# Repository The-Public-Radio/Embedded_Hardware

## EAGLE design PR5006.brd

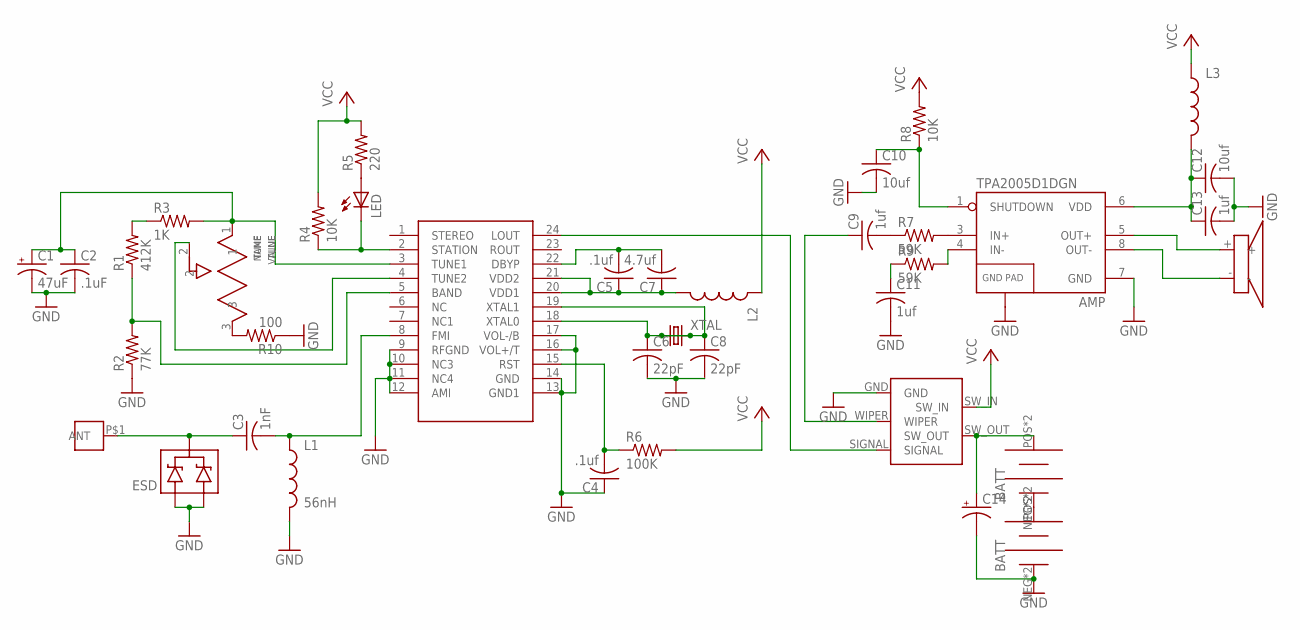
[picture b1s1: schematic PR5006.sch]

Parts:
AMP: TPA2005D1DGN; POWER-SOP8
C1: 47uF; E2-5
C2: .1uF; C0603
C3: 1nF; C0603
C4, C5: .1uf; C0603
C6, C8: 22pF; C0603
C7: 4.7uf; C0603
C9, C11, C13: 1uf; C0603
C10, C12: 10uf; C0603
C14: CPOL-USE2.5-5; E2,5-5
ESD: MMBZ27VCLT1; SOT23-3
L1: 56nH; 0603
L2, L3: INDUCTOR0603; 0603
LED: LEDCHIP-LED0603; CHIP-LED0603
R1: 412K; R0603
R2: 77K; R0603
R3: 1K; R0603
R4, R8: 10K; R0603
R5: 220; R0603
R6: 100K; R0603
R7, R9: 59K; R0603
R10: 100; R0603
SI4831: SI4831-SSOP-24
TUNE: TUNE; 64XR_BOURNS_TRIMPOT
U$1, U$2: BK-92_MPD_AA_BATT_CLIP
U$3: CE32A_DAYTON_SPKR
U$4: M3_SCREW_POST
U$5: P170_BOURNS_POT_SW
XTAL: CRYSTAL32-SMD; CRYSTAL-32KHZ-SMD

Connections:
GND: AMP.7 (GND), AMP.9 (GND), C1.-, C2.2, C4.1, C6.2, C8.2, C10.2, C11.2, C12.2, C13.2, C14.-, ESD.1 (A1), ESD.2 (A2), L1.2, R2.1, R10.1, SI4831.9 (RFGND), SI4831.10 (NC3), SI4831.11 (NC4), SI4831.12 (AMI), SI4831.13 (GND1), SI4831.14 (GND), SI4831.16 (VOL+/T), SI4831.17 (VOL-/B), U$2.NEG, U$2.NEG@2 (NEG), U$5.GND
unnamed: AMP.3 (IN+), R7.2
unnamed: AMP.4 (IN-), R9.2
unnamed: C11.1, R9.1
unnamed: C9.2, R7.1
unnamed: SI4831.24 (LOUT), U$5.SIGNAL
unnamed: C5.2, C7.2, SI4831.22 (DBYP)
unnamed: C8.1, SI4831.19 (XTAL1), XTAL.X1 (1)
unnamed: C4.2, R6.1, SI4831.15 (RST)
unnamed: LED.C, R4.1, SI4831.2 (STATION)
unnamed: C6.1, SI4831.18 (XTAL0), XTAL.X2 (2)
unnamed: LED.A, R5.1
unnamed: SI4831.4 (TUNE2), TUNE.2
unnamed: R1.1, R2.2, SI4831.5 (BAND)
unnamed: U$1.NEG, U$1.NEG@2 (NEG), U$2.POS, U$2.POS@2 (POS)
unnamed: C3.2, L1.1, SI4831.8 (FMI)
unnamed: C5.1, C7.1, L2.2, SI4831.20 (VDD1), SI4831.21 (VDD2)
unnamed: AMP.6 (VDD), C12.1, C13.1, L3.2
unnamed: AMP.1 (SHUTDOWN), C10.1, R8.1
unnamed 19: C3.1, ESD.3 (C), U$4.P$1; also elsewhere on the board
unnamed: R1.2, R3.1
unnamed: C1.+, C2.1, R3.2, SI4831.3 (TUNE1), TUNE.1
unnamed: AMP.5 (OUT+), U$3.+
unnamed: AMP.8 (OUT-), U$3.-
unnamed: C9.1, U$5.WIPER
unnamed: R10.2, TUNE.3
unnamed: C14.+, U$1.POS, U$1.POS@2 (POS), U$5.SW_OUT
VCC: L2.1, L3.1, R4.2, R5.2, R6.2, R8.2, U$5.SW_IN

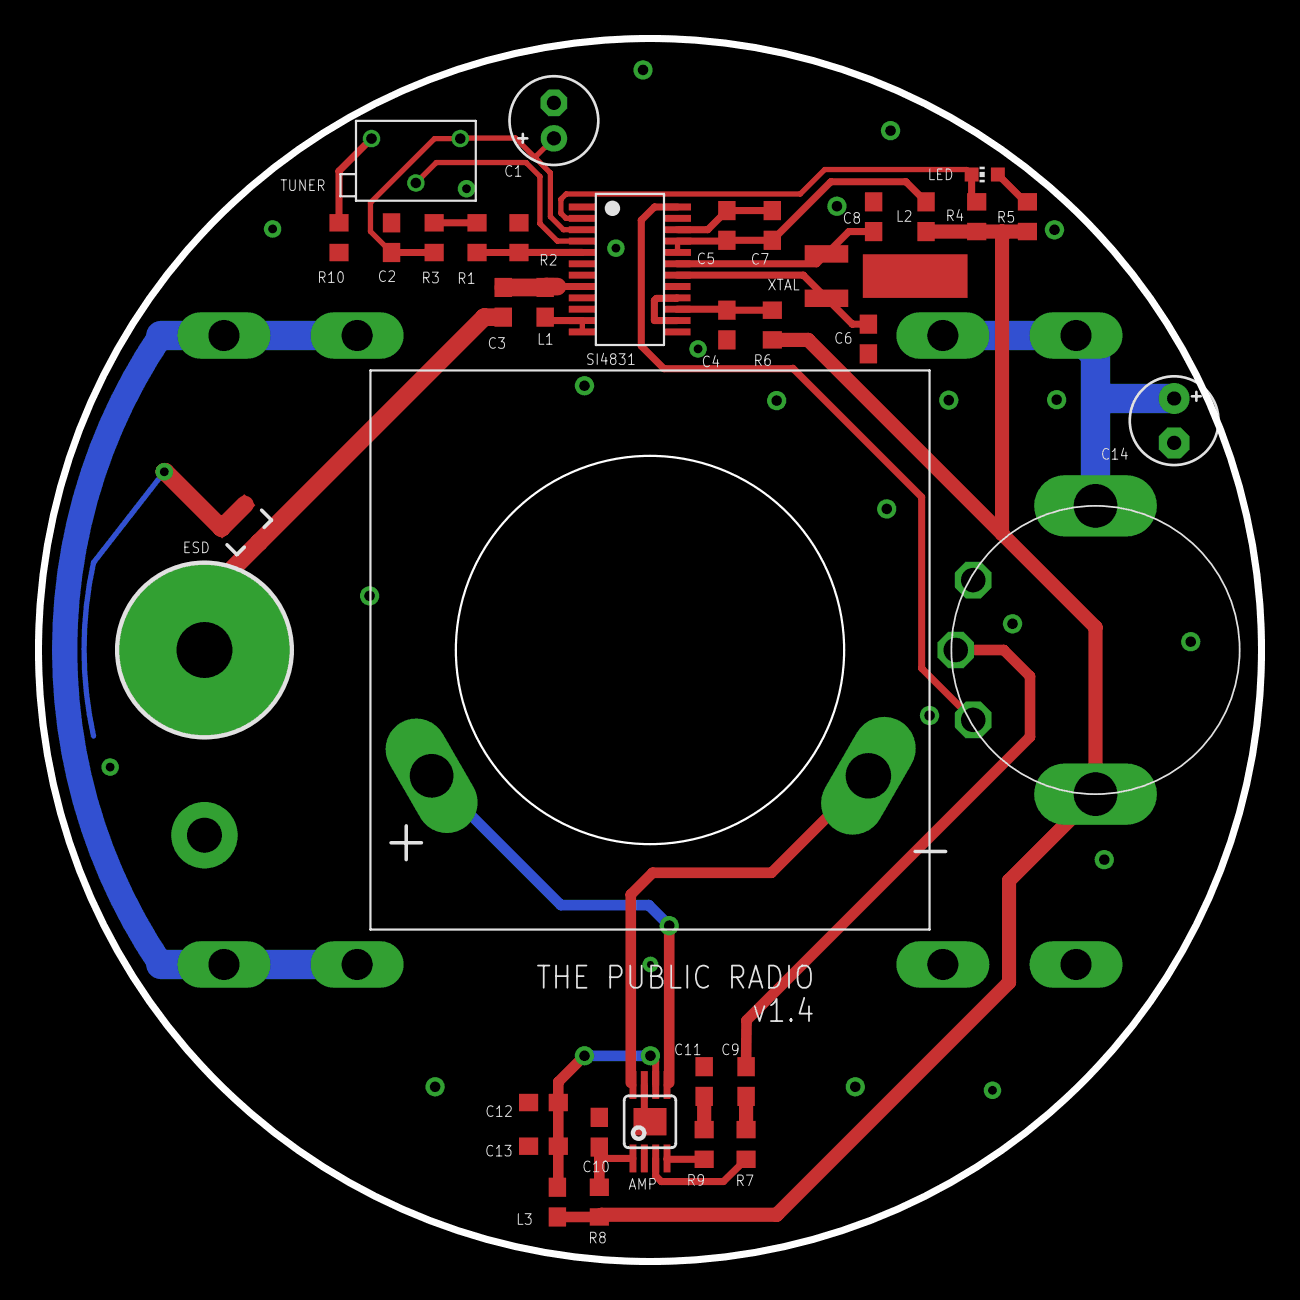
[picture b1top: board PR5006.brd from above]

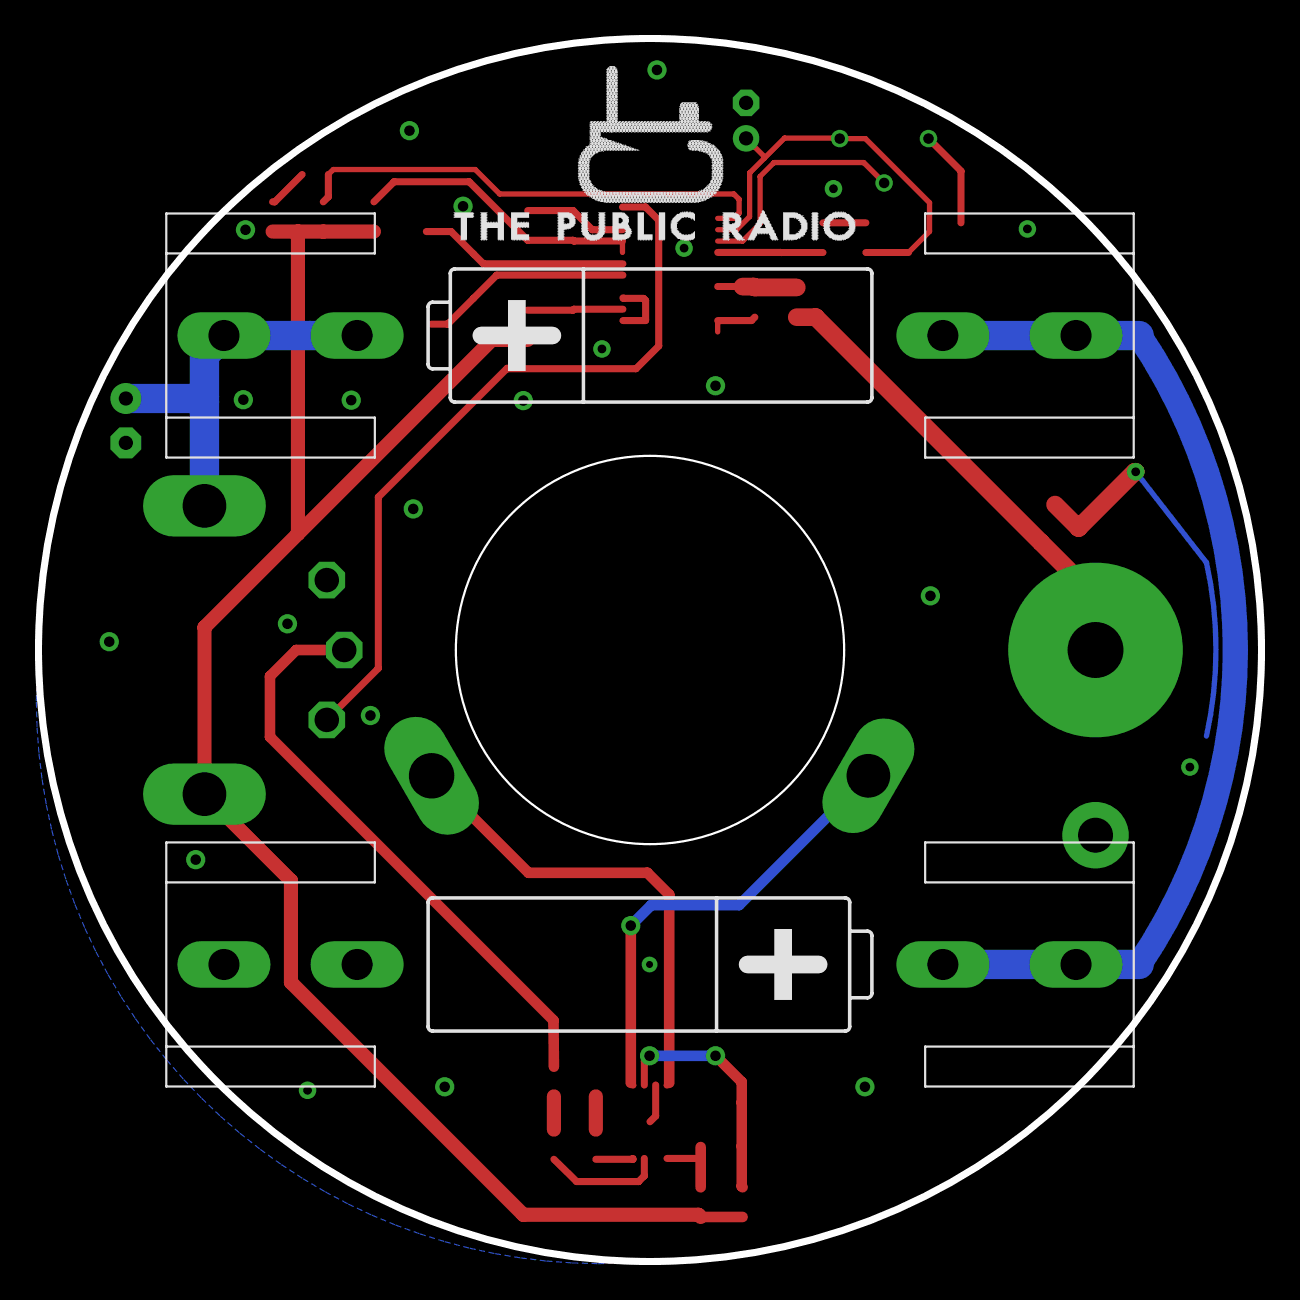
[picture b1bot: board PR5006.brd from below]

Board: 2 copper layers, 70.0 x 70.0 mm, 38 parts (2 on the bottom side), 28 nets.

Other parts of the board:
ANT: M3_SCREW_POST

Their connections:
unnamed 19: ANT.P$1; also elsewhere on the board

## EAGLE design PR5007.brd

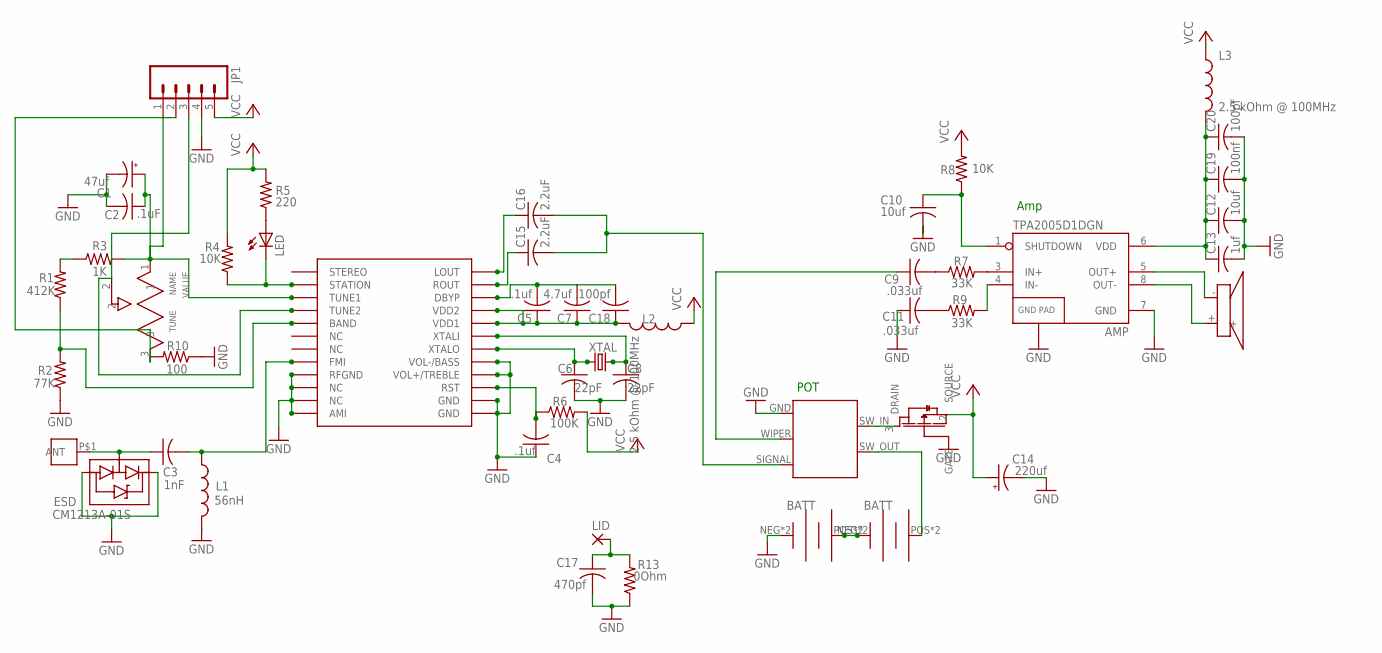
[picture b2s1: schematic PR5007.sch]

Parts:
AMP: TPA2005D1DGN; POWER-SOP8
ANT: M3_SCREW_POST
C1: 47uf; E2-5
C2: .1uF; C0603
C3: 1nF; C0603
C4, C5: .1uf; C0603
C6, C8: 22pF; C0603
C7: 4.7uf; C0603
C9, C11: .033uf; C0603
C10, C12: 10uf; C0603
C13: 1uf; C0603
C14: 220uf; E2-5
C15, C16: 2.2uF; C0603
C17: 470pf; C0805
C18, C20: 100pf; C0603
C19: 100nf; C0603
ESD: CM1213A-01S; SOT23-3
FET: SI2333DDS
JP1: M05LOCK; 1X05_LOCK
L1: 56nH; 0603
L2, L3: 2.5 kOhm @ 100MHz; 0603
LED: LEDCHIPLED_0805; CHIPLED_0805
LID: 2,54/1,0
R1: 412K; R0603
R2: 77K; R0603
R3: 1K; R0603
R4, R8: 10K; R0603
R5: 220; R0603
R6: 100K; R0603
R7, R9: 33K; R0603
R10: 100; R0603
R13: 0Ohm; R0603
TUNE: TUNE; 64XR_BOURNS_TRIMPOT
U$1, U$2: BK-92_MPD_AA_BATT_CLIP
U$3: CE32A_DAYTON_SPKR
U$4: SI4831_FM_IC
U$5: RV170SF_TAIWANA_POT_SW
XTAL: CRYSTAL32-SMD; CRYSTAL-32KHZ-SMD

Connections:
GND: AMP.7 (GND), AMP.9 (GND), C1.-, C2.2, C4.1, C6.2, C8.2, C10.2, C11.1, C12.2, C13.2, C14.-, C17.2, C19.2, C20.2, ESD.2 (VP), ESD.3 (VN), FET.1 (GATE), JP1.4, L1.2, R2.1, R10.1, R13.1, U$2.NEG, U$2.NEG@2 (NEG), U$4.AMI, U$4.GND, U$4.GND@2 (GND), U$4.NC@3 (NC), U$4.NC@4 (NC), U$4.RFGND, U$4.VOL+/TREBLE, U$4.VOL-/BASS, U$5.GND
unnamed: AMP.3 (IN+), R7.2
unnamed: AMP.4 (IN-), R9.2
unnamed: C11.2, R9.1
unnamed: C9.2, R7.1
unnamed: C15.2, C16.2, U$5.SIGNAL
unnamed: C5.2, C7.2, C18.2, U$4.DBYP
unnamed: C8.1, U$4.XTALI, XTAL.X1 (1)
unnamed: C4.2, R6.1, U$4.RST
unnamed: LED.C, R4.1, U$4.STATION
unnamed: C6.1, U$4.XTALO, XTAL.X2 (2)
unnamed: LED.A, R5.1
unnamed: JP1.3, TUNE.2, U$4.TUNE2
unnamed: R1.1, R2.2, U$4.BAND
unnamed: U$1.NEG, U$1.NEG@2 (NEG), U$2.POS, U$2.POS@2 (POS)
unnamed: C3.2, L1.1, U$4.FMI
unnamed: C5.1, C7.1, C18.1, L2.2, U$4.VDD1, U$4.VDD2
unnamed: AMP.6 (VDD), C12.1, C13.1, C19.1, C20.1, L3.2
unnamed: AMP.1 (SHUTDOWN), C10.1, R8.1
unnamed: ANT.P$1, C3.1, ESD.1 (CH)
unnamed: R1.2, R3.1
unnamed: U$1.POS, U$1.POS@2 (POS), U$5.SW_OUT
unnamed: C1.+, C2.1, JP1.1, R3.2, TUNE.1, U$4.TUNE1
unnamed: AMP.5 (OUT+), U$3.-
unnamed: AMP.8 (OUT-), U$3.+
unnamed: C9.1, U$5.WIPER
unnamed: JP1.2, R10.2, TUNE.3
unnamed: FET.3 (DRAIN), U$5.SW_IN
unnamed: C15.1, U$4.ROUT
unnamed: C16.1, U$4.LOUT
unnamed: C17.1, LID.1, R13.2
VCC: C14.+, FET.2 (SOURCE), JP1.5, L2.1, L3.1, R4.2, R5.2, R6.2, R8.2

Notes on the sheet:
Amp
POT

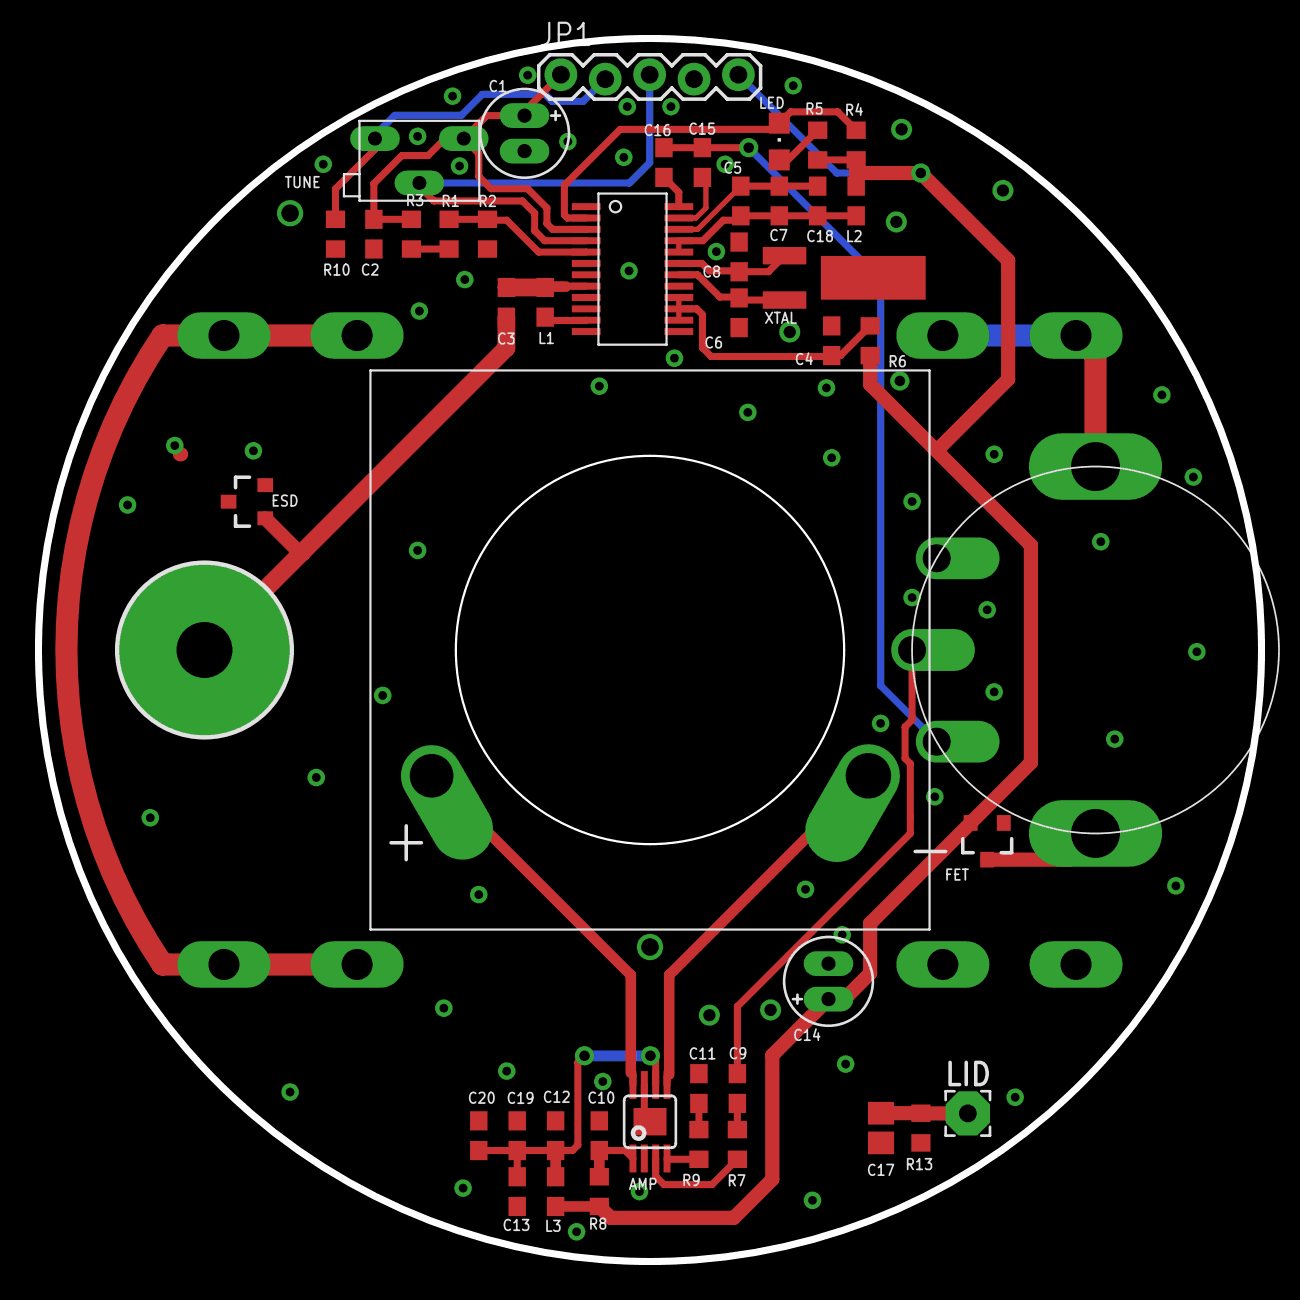
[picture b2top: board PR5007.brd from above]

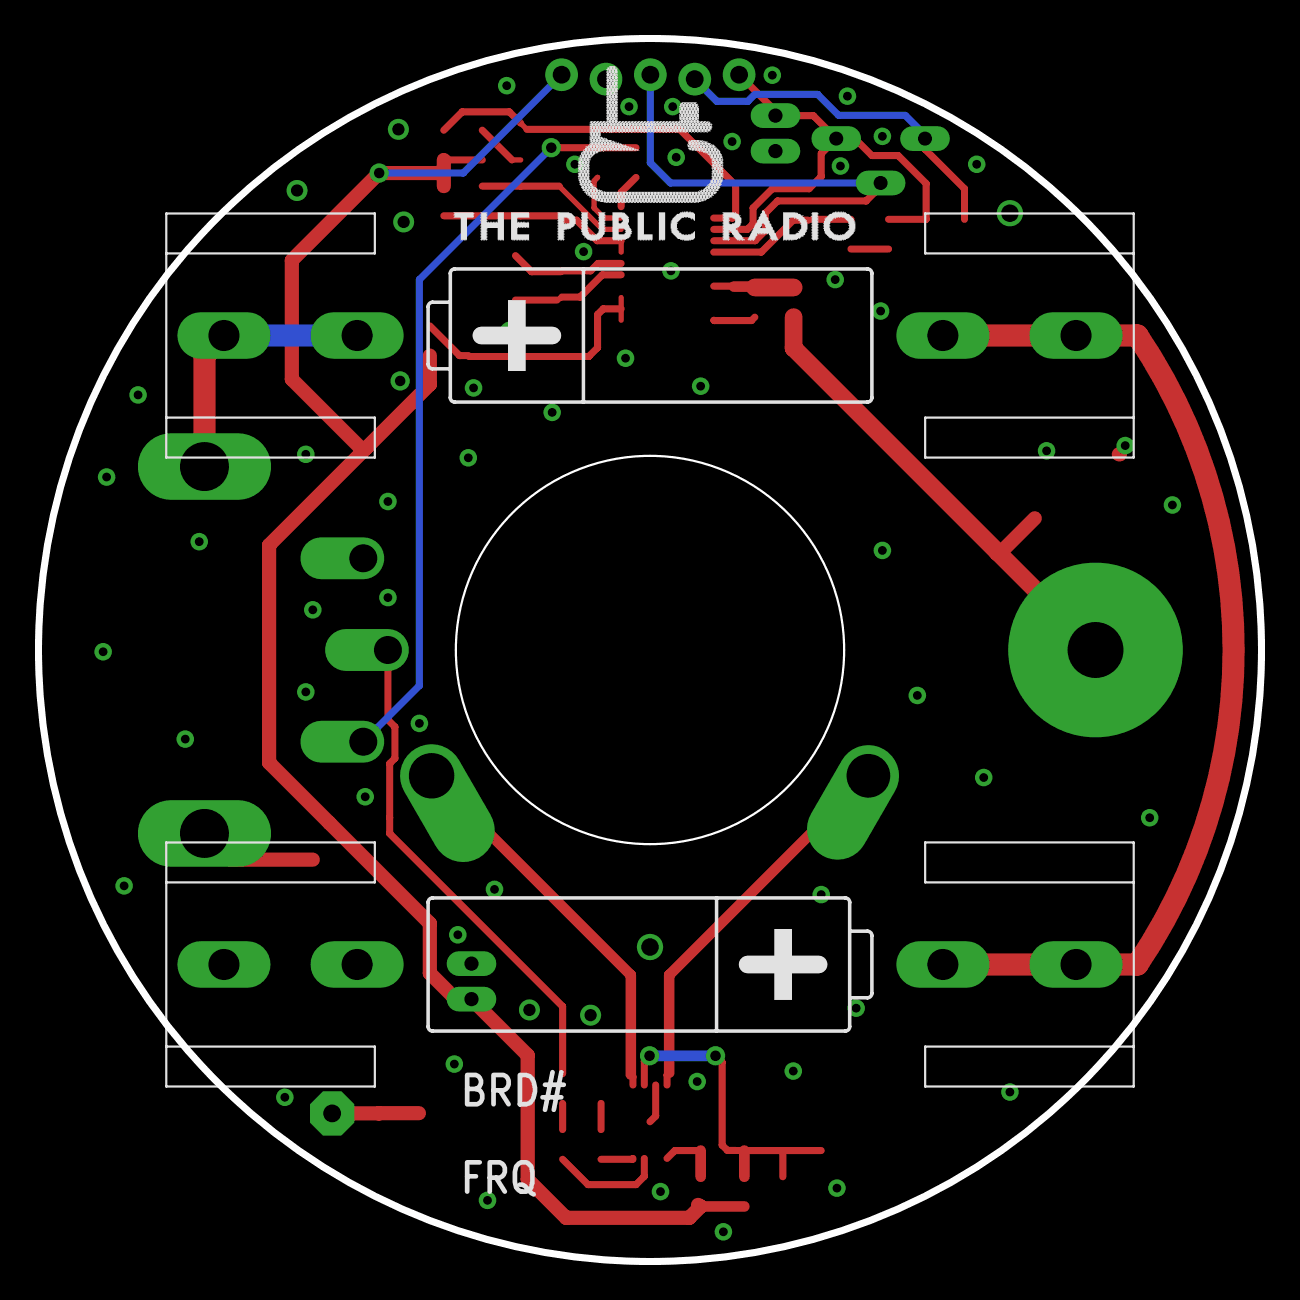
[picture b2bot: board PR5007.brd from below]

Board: 2 copper layers, 70.0 x 70.0 mm, 48 parts (2 on the bottom side), 32 nets.

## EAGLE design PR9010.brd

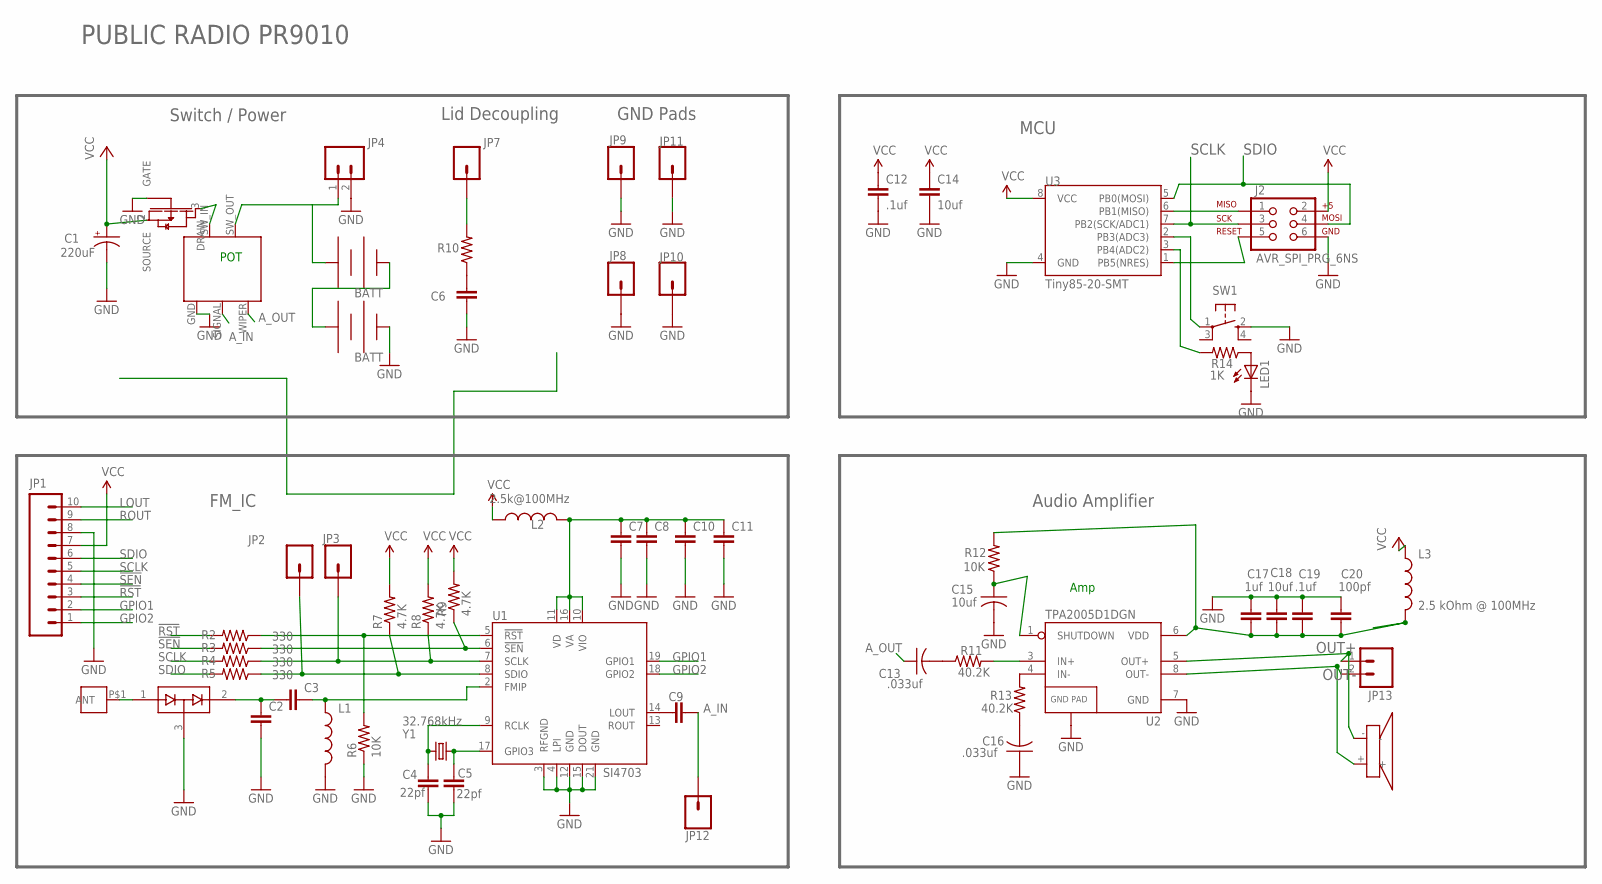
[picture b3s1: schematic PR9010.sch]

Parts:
C1: 220uF; PANASONIC_C
C2, C3, C7, C8, C9, C10, C11: 1.0uF; 0805
C4, C5: 22pf; 0805
C6: CAP0805; 0805
C12, C19: .1uf; 0805
C13, C16: .033uf; C0603
C14, C18: 10uf; 0805
C15: 10uf; C0603
C17: 1uf; 0805
C20: 100pf; 0805
D1: BAV99; SOT23
FET1: SI2333DDS
J1: M3_SCREW_POST
J2: AVR_SPI_PRG_6NS; 2X3-NS
JP1: M10"; 1X10
JP2, JP3, JP7, JP8, JP9, JP10, JP11, JP12: M01PTH; 1X01
JP4, JP13: M02PTH3; 1X02_LONGPADS
JP5, JP6: BK-92_MPD_AA_BATT_CLIP
L1: INDUCTOR0805; 0805
L2: 2.5k@100MHz; 0603
L3: 2.5 kOhm @ 100MHz; 0603
LED1: LEDSML0603; SML0603
R1: RV170SF_TAIWANA_POT_SW
R2, R3, R4, R5: 330; 0805
R6: 10K; 0805
R7, R8, R9: 4.7K; 0805
R10: RESISTOR0805-RES; 0805
R11, R13: 40.2K; R0603
R12: 10K; R0603
R14: 1K; R0603
SW1: SPST_TACT-KMR2; KMR2
U1: SI4703; SPARKFUN_SI470X
U2: TPA2005D1DGN; POWER-SOP8
U3: Tiny85-20-SMT; SO08-EIAJ
U$3: CE32A_DAYTON_SPKR
Y1: 32.768kHz; CRYSTAL-32KHZ-SMD

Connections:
3.3V: JP1.7, R7.2, R8.2, R9.2
!RST: JP1.3, R2.2
!RST-L: R2.1, R6.2, U1.5 (!RST)
!SEN: JP1.4, R3.2
!SEN-L: R3.1, R9.1, U1.6 (!SEN)
A_IN: C9.2, JP12.1, R1.SIGNAL
A_OUT: C13.1, R1.WIPER
GND: C1.-, C2.2, C4.2, C5.2, C6.2, C7.2, C8.2, C10.2, C11.2, C12.2, C14.2, C15.2, C16.1, C17.1, C18.1, C19.1, C20.1, D1.3 (COM), FET1.1 (GATE), J2.6, JP1.8, JP4.2, JP6.NEG, JP6.NEG@2 (NEG), JP8.1, JP9.1, JP10.1, JP11.1, L1.2, LED1.C, R1.GND, R6.1, SW1.2 (S), U1.3 (RFGND), U1.4 (LPI), U1.12 (GND), U1.15 (DOUT), U1.21 (GND), U2.7 (GND), U2.9 (GND), U3.4 (GND)
GPIO1: JP1.2, U1.19 (GPIO1)
GPIO2: JP1.1, U1.18 (GPIO2)
LOUT: C9.1, JP1.10, U1.14 (LOUT)
unnamed: C4.1, U1.9 (RCLK), Y1.X2 (2)
unnamed: C5.1, U1.17 (GPIO3), Y1.X1 (1)
unnamed: C13.2, R11.1
unnamed: R11.2, U2.3 (IN+)
unnamed: R13.2, U2.4 (IN-)
unnamed: C3.2, L1.1, U1.2 (FMIP)
unnamed: LED1.A, R14.1
unnamed: JP7.1, R10.2
unnamed: C7.1, C8.1, C10.1, C11.1, L2.2, U1.10 (VIO), U1.11 (VD), U1.16 (VA)
unnamed: SW1.1, U3.2 (PB3(ADC3))
unnamed: R14.2, U3.3 (PB4(ADC2))
unnamed: JP5.NEG, JP5.NEG@2 (NEG), JP6.POS, JP6.POS@2 (POS)
unnamed: D1.1 (A1), J1.P$1
unnamed: JP4.1, JP5.POS, JP5.POS@2 (POS), R1.SW_OUT
unnamed: C2.1, C3.1, D1.2 (C2)
unnamed: C17.2, C18.2, C19.2, C20.2, L3.2, R12.2, U2.6 (VDD)
unnamed: C15.1, R12.1, U2.1 (SHUTDOWN)
unnamed: C16.2, R13.1
unnamed: FET1.3 (DRAIN), R1.SW_IN
unnamed: C6.1, R10.1
OUT+: JP13.1, U2.5 (OUT+), U$3.-
OUT-: JP13.2, U2.8 (OUT-), U$3.+
PB1: J2.1, U3.6 (PB1(MISO))
PB5: J2.5, U3.1 (PB5(NRES))
ROUT: JP1.9
SCLK: J2.3, JP1.5, R4.2, U3.7 (PB2(SCK/ADC1))
SCLK-L: JP3.1, R4.1, R8.1, U1.7 (SCLK)
SDIO: J2.4, JP1.6, R5.2, U3.5 (PB0(MOSI))
SDIO-L: JP2.1, R5.1, R7.1, U1.8 (SDIO)
VCC: C1.+, C12.1, C14.1, FET1.2 (SOURCE), J2.2, L2.1, L3.1, U3.8 (VCC)

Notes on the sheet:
Amp
POT
FM_IC
Switch / Power
Lid Decoupling
Audio Amplifier
MCU
PUBLIC RADIO PR9010
GND Pads

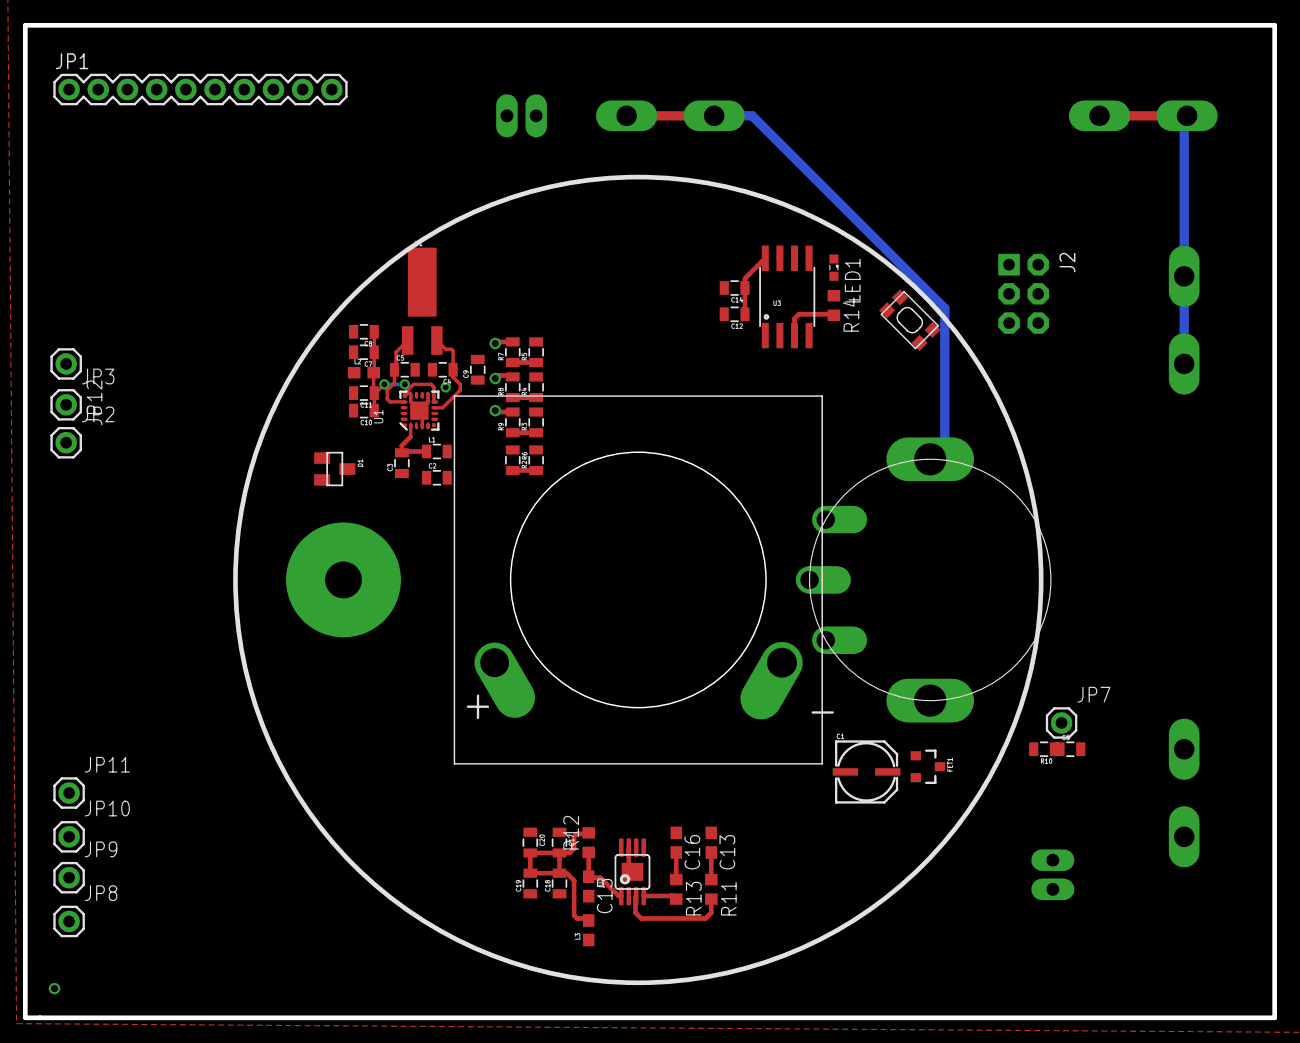
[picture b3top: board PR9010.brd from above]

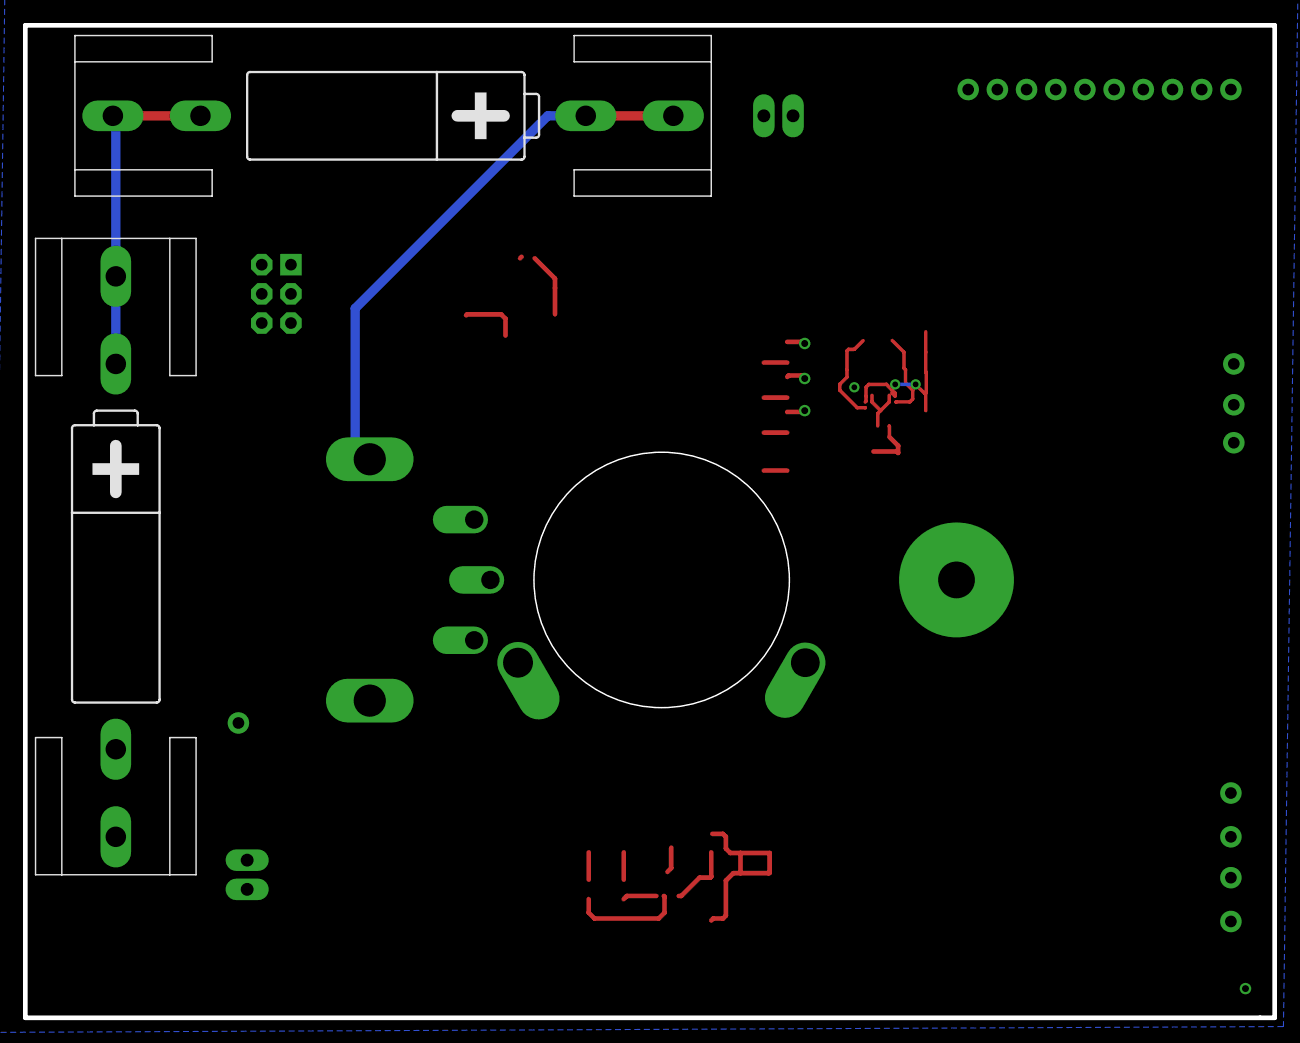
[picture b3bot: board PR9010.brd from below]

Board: 2 copper layers, 108.7 x 86.4 mm, 61 parts (2 on the bottom side), 40 nets.

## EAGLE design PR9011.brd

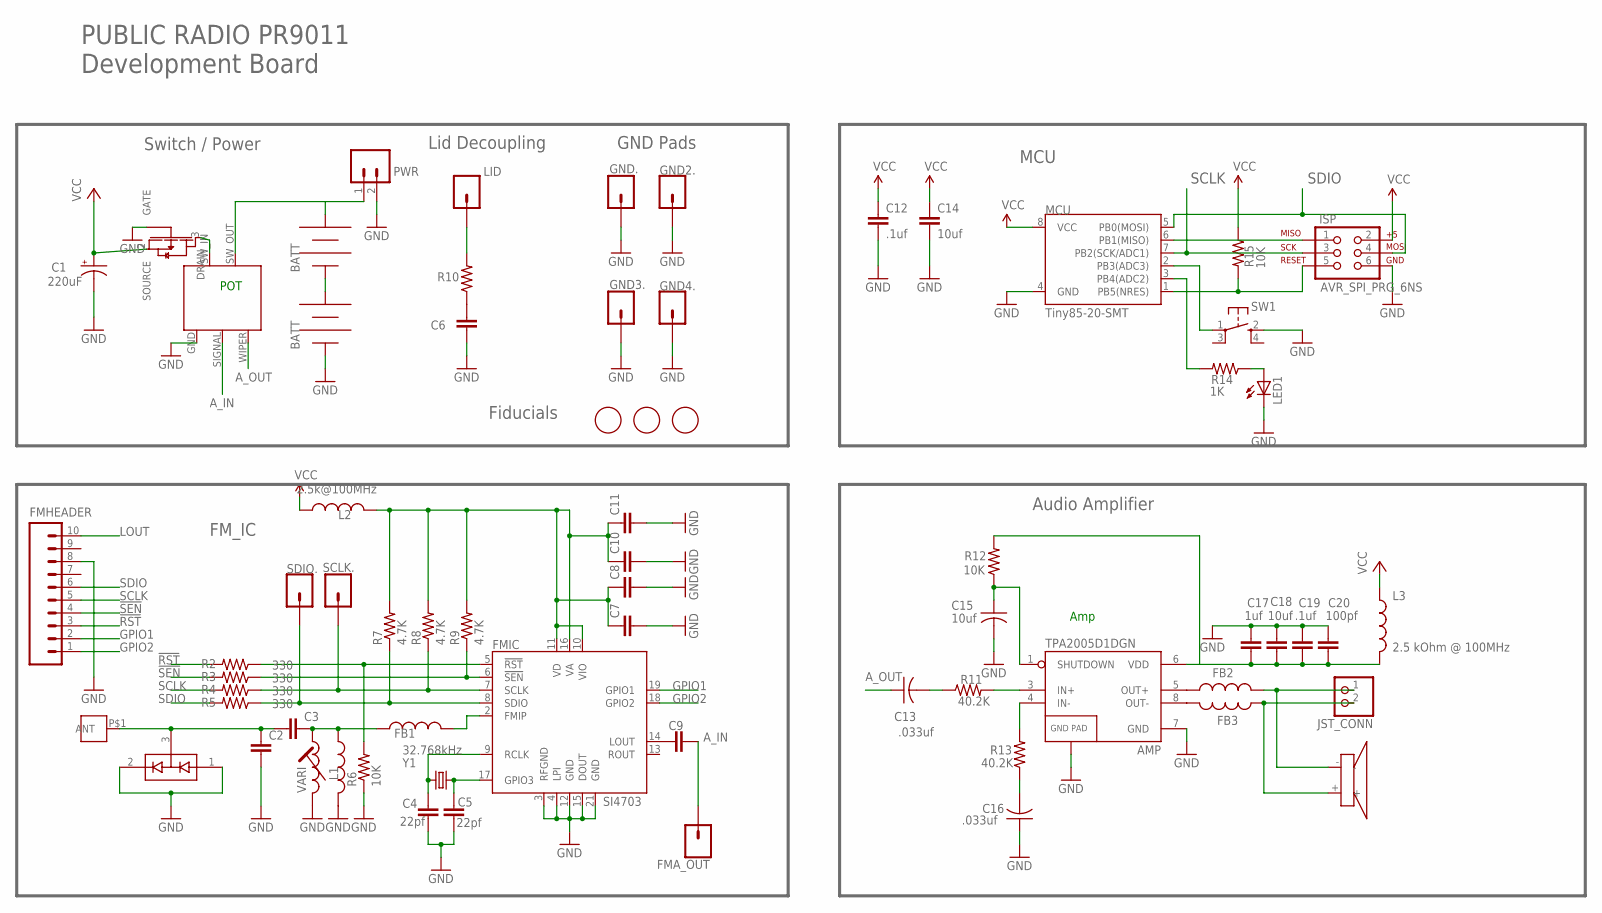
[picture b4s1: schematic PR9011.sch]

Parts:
AMP: TPA2005D1DGN; POWER-SOP8
C1: 220uF; PANASONIC_C
C2, C3, C7, C9: 1.0uF; 0805
C4, C5: 22pf; 0805
C6: CAP0805; 0805
C8: .1uF; 0805
C10: 22nF; 0805
C11: 4.7uF; 0805
C12, C19: .1uf; 0805
C13, C16: .033uf; C0603
C14, C18: 10uf; 0805
C15: 10uf; C0603
C17: 1uf; 0805
C20: 100pf; 0805
D1: BAV99; SOT23-3
FB1, FB2, FB3: INDUCTOR0805; 0805
FET1: SI2333DDS
FMA_OUT: M01PTH; 1X01
FMHEADER: M10LOCK; 1X10_LOCK
FMIC: SI4703; SPARKFUN_SI470X
GND2., GND3., GND4., GND.: M01PTH; 1X01
ISP: AVR_SPI_PRG_6NS; 2X3-NS
J1: M3_SCREW_POST
JP5, JP6: BK-92_MPD_AA_BATT_CLIP
JST_CONN: JST_2PIN-SMT-RA; JST-PH-2-SMT-RA
L1: INDUCTOR0805; 0805
L2: 2.5k@100MHz; 0603
L3: 2.5 kOhm @ 100MHz; 0603
LED1: LEDSML0603; SML0603
LID: M01PTH; 1X01
MCU: Tiny85-20-SMT; SO08-EIAJ
PWR: M02PTH3; 1X02_LONGPADS
R1: RV170SF_TAIWANA_POT_SW
R2, R3, R4, R5: 330; 0805
R6: 10K; 0805
R7, R8, R9: 4.7K; 0805
R10: RESISTOR0805-RES; 0805
R11, R13: 40.2K; R0603
R12, R15: 10K; R0603
R14: 1K; R0603
SCLK.: M01PTH; 1X01
SDIO.: M01PTH; 1X01
SW1: SPST_TACT-KMR2; KMR2
U$1, U$2, U$4: FIDUCIAL; FIDUCIAL_1MM
U$3: CE32A_DAYTON_SPKR
VARI: L-TRIM; 146/150
Y1: 32.768kHz; CRYSTAL-32KHZ-SMD

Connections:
3.3V: C7.1, C8.1, C10.1, C11.1, FMIC.10 (VIO), FMIC.11 (VD), FMIC.16 (VA), L2.2, R7.2, R8.2, R9.2
!RST: FMHEADER.3, R2.2
!RST-L: FMIC.5 (!RST), R2.1, R6.2
!SEN: FMHEADER.4, R3.2
!SEN-L: FMIC.6 (!SEN), R3.1, R9.1
A_IN: C9.2, FMA_OUT.1, R1.SIGNAL
A_OUT: C13.1, R1.WIPER
GND: AMP.7 (GND), AMP.9 (GND), C1.-, C2.2, C4.2, C5.2, C6.2, C7.2, C8.2, C10.2, C11.2, C12.2, C14.2, C15.2, C16.1, C17.1, C18.1, C19.1, C20.1, D1.1 (A1), D1.2 (C2), FET1.1 (GATE), FMHEADER.8, FMIC.3 (RFGND), FMIC.4 (LPI), FMIC.12 (GND), FMIC.15 (DOUT), FMIC.21 (GND), GND2..1, GND3..1, GND4..1, GND..1, ISP.6, JP6.NEG, JP6.NEG@2 (NEG), L1.2, LED1.C, MCU.4 (GND), PWR.2, R1.GND, R6.1, SW1.2 (S), VARI.P$1 (START)
GPIO1: FMHEADER.2, FMIC.19 (GPIO1)
GPIO2: FMHEADER.1, FMIC.18 (GPIO2)
LOUT: C9.1, FMHEADER.10, FMIC.14 (LOUT)
unnamed: C4.1, FMIC.9 (RCLK), Y1.X2 (2)
unnamed: C5.1, FMIC.17 (GPIO3), Y1.X1 (1)
unnamed: C13.2, R11.1
unnamed: AMP.3 (IN+), R11.2
unnamed: AMP.4 (IN-), R13.2
unnamed: FB1.2, FMIC.2 (FMIP)
unnamed: LED1.A, R14.1
unnamed: LID.1, R10.2
unnamed: FB2.2, JST_CONN.1 (2), U$3.-
unnamed: MCU.2 (PB3(ADC3)), SW1.1
unnamed: MCU.3 (PB4(ADC2)), R14.2
unnamed: JP5.NEG, JP5.NEG@2 (NEG), JP6.POS, JP6.POS@2 (POS)
unnamed: C2.1, C3.1, D1.3 (COM), J1.P$1
unnamed: JP5.POS, JP5.POS@2 (POS), PWR.1, R1.SW_OUT
unnamed: C3.2, FB1.1, L1.1, VARI.P$2 (END)
unnamed: AMP.8 (OUT-), FB3.2
unnamed: AMP.6 (VDD), C17.2, C18.2, C19.2, C20.2, L3.2, R12.2
unnamed: AMP.5 (OUT+), FB2.1
unnamed: AMP.1 (SHUTDOWN), C15.1, R12.1
unnamed: C16.2, R13.1
unnamed: FET1.3 (DRAIN), R1.SW_IN
unnamed: C6.1, R10.1
OUT-: FB3.1, JST_CONN.2 (1), U$3.+
PB1: ISP.1, MCU.6 (PB1(MISO))
PB5: ISP.5, MCU.1 (PB5(NRES)), R15.2
SCLK: FMHEADER.5, ISP.3, MCU.7 (PB2(SCK/ADC1)), R4.2
SCLK-L: FMIC.7 (SCLK), R4.1, R8.1, SCLK..1
SDIO: FMHEADER.6, ISP.4, MCU.5 (PB0(MOSI)), R5.2
SDIO-L: FMIC.8 (SDIO), R5.1, R7.1, SDIO..1
VCC: C1.+, C12.1, C14.1, FET1.2 (SOURCE), ISP.2, L2.1, L3.1, MCU.8 (VCC), R15.1

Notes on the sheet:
Amp
POT
FM_IC
Switch / Power
Lid Decoupling
Audio Amplifier
MCU
PUBLIC RADIO PR9011 Development Board
GND Pads
Fiducials

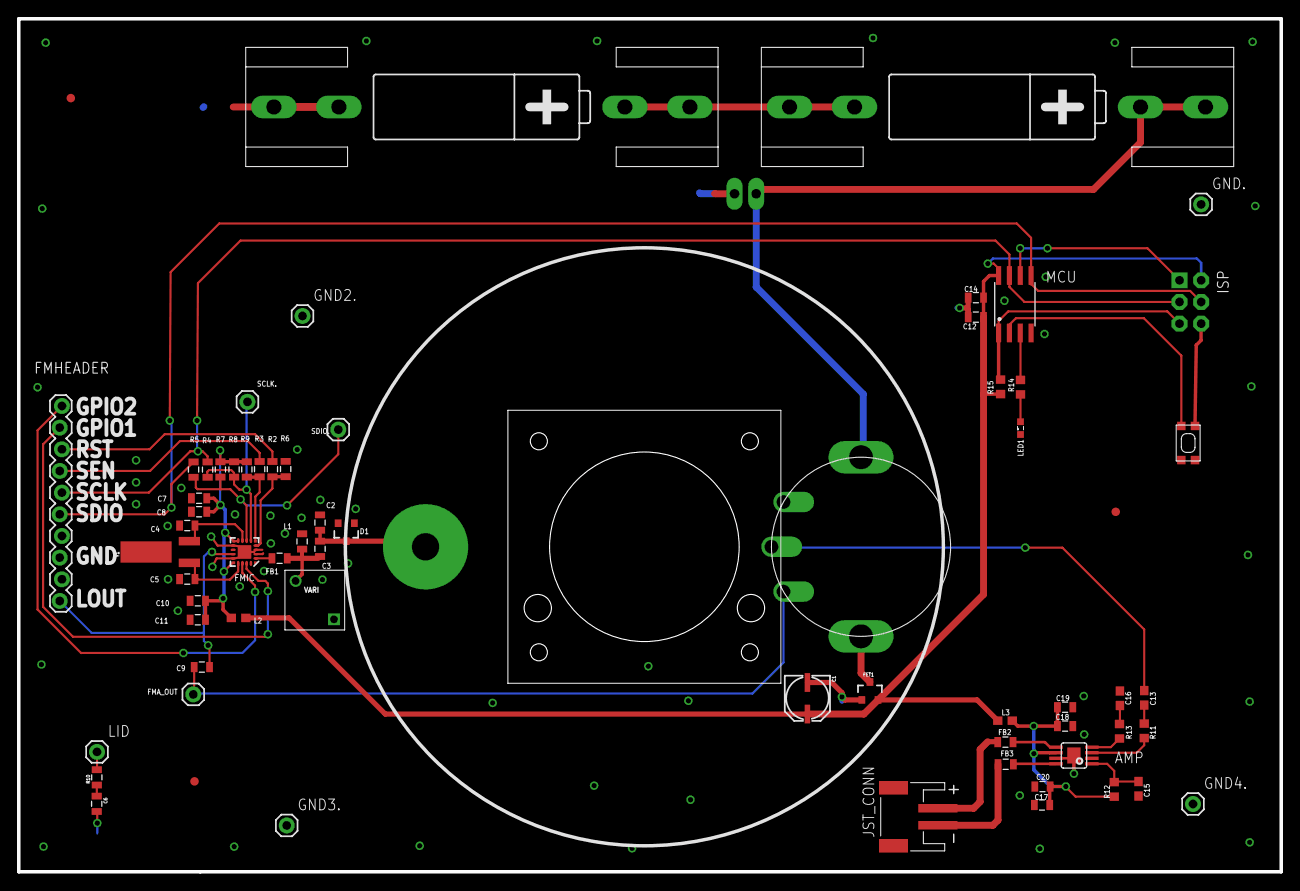
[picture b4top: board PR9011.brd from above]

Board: 2 copper layers, 148.0 x 100.0 mm, 69 parts (0 on the bottom side), 41 nets.

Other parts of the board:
U$5: CE32A_FOR_JST

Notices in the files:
parts and their libraries:
SparkFun-AnalogIC: Licensing: CC v3.0 Share-Alike You are welcome to use this library for commercial purposes.
SparkFun-DigitalIC: Licensing: Creative Commons ShareAlike 4.0 International - https://creativecommons.org/licenses/by-sa/4.0
